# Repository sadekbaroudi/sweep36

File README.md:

# Name

sweep36

A 36 key version of the sweep, maintaining the original diodeless pcb.

# Variations

## sweeeeep

why the name sweeeeep? because an elite-c is required to support the extra features, and an elite-c has 5 additional pins... so 5 Es for the 5 extra pins. Yes, it's dumb, I know.

### Descripiton

This is a reversible pcb that is wired only, has per key leds (only on one of the two variations), oled, and choc spacing. In order to continue to support a no diode setup, I added support for the elite-c, and this is now required for the build. You can use alternative elite-c compatible controllers.

### Versions and features

There are 6 versions of this pcb, as found in the pcb/wired-rgb directory:
* choc: No hotswap, 36 keys
* choc-rotated-inner-thumb: No hotswap, 36 keys, rotated inner thumb similar to the corne
* choc-hotswap: Hotswap only, 36 keys
* ks27-choc: Support for both choc and gateron ks-27 switches, no hotswap. Note that ks-27 switches use MX keycaps on a low profile switch. Given it's choc spacing, you will likely need to use custom smaller MX keycaps if using these switches
* choc-evq-inside: No hotswap, 34 key, with an evqwgd001 roller encoder on the inside thumb key
* choc-evq-outside: No hotswap, 34 key, with an evqwgd001 roller encoder on the outside thumb key

## swweeep

So, to keep the silliness going, this is has an extra W for the wireless only, and 3 Es for the 3 extra required pins on the nice!nano.

### Description (and story)

This was created after the sweeeeep as a wireless alternative. Given the nice!nano has two less gpio than the elite-c, had to remove the data pin (and therefore TRRS). So, this is wireless only!

Given it's a wireless only build, it made sense to add nice!view support, given it consumes 1000x less power than the typical OLED. That meant that it would consume one too many gpio. In the spirit of low power consumption, removing per key rgb was a natural decision, leaving it with just enough gpio for this board.

So, backstory aside, the net of it is:
* nice!nano required
* nice!view support
* wireless only (no TRRS)
* JST spaced battery through holes
* on/off switch
* both kailh hotswap and mill max compatible through hole

Special thanks to @jasonhazel for kickstarting the initiative!

### Notes

Regarding the JST footprint, you can solder directly or use jst. If soldering, connect power to the middle hole (with the +) and GND to the -. If using JST, be sure to look at your battery wiring and connect the JST connector such that the power lines up with the middle pin (again, with thhe + on the silkscreen)

It is possible to also produce a PCB baseplate board for the swweeep with a nice silkscreen, the kicad files are [here](https://github.com/sadekbaroudi/sweep36/tree/master/sweeeeep), or if you think the [Great Wave Off Kanagawa](https://en.wikipedia.org/wiki/The_Great_Wave_off_Kanagawa) would make a good silkscreen, the gerbers for that are [here](https://github.com/sadekbaroudi/sweep36/blob/master/swweeep/swweeep-base/gerber/v1.0-kanagawa-gerbers.zip)

## dweeeeep

### Description

This was created after both of the other variations. It was created as an alternative to the sweeeeep. It's a sweeeeep with diodes. I know the principle of the original sweep was to have no diodes. I apologize, this was a special request to allow people to use a pro micro compatible controller, as they're much cheaper.

# Support me!

I have spent a lot of time and money designing prototypes, testing, developing, etc. Any contributions would be greatly appreciated!

If you don't want to, or can't afford to support me, please send me a message to let me know you've built one, along with pictures. Also, feel free to submit a pull request with pictures into this repository. I'd be happy to showcase your build.

Reddit: /u/sadekbaroudi
Discord: sadekbaroudi#1258

# Firmware

## Vial (wired version only)

Special thanks to [Jason Hazel](https://github.com/jasonhazel) for adding vial support. Note that given vial with split code takes up most of the space, there is no support for the OLED or per key RGB. If you want those features, please use QMK below.

https://github.com/sadekbaroudi/vial-qmk/tree/vial/keyboards/fingerpunch/sweeeeep

## QMK (wired version only)

https://github.com/sadekbaroudi/qmk_firmware/tree/master/keyboards/fingerpunch/sweeeeep

## ZMK (wireless version only)

https://github.com/sadekbaroudi/zmk-swweeep

# swweeep v1.3 fix

If you built a swweeep v1.3 or earlier, you will need to connect the battery ground pin to the controller gnd pin, as shown below:

# Pictures

## swweeep with nice!view

## swweeep with the base plate

## sweeeeep choc

## sweeeeep evq inside

### sweeeeep (choc)
| Front | Back |
| :---: | :---: |
|  |  |

### sweeeeep (choc-evq-inside)
| Front | Back |
| :---: | :---: |
|  |  |

### sweeeeep (choc-evq-outside)
| Front | Back |
| :---: | :---: |
|  |  |

### sweeeeep (choc-hotswap)
| Front | Back |
| :---: | :---: |
|  |  |

### sweeeeep (choc-rotated-inner-thumb)
| Front | Back |
| :---: | :---: |
|  |  |

### sweeeeep (ks27-choc)
| Front | Back |
| :---: | :---: |
|  |  |

### swweeep (choc-hotswap-optional)
| Front | Back |
| :---: | :---: |
|  |  |

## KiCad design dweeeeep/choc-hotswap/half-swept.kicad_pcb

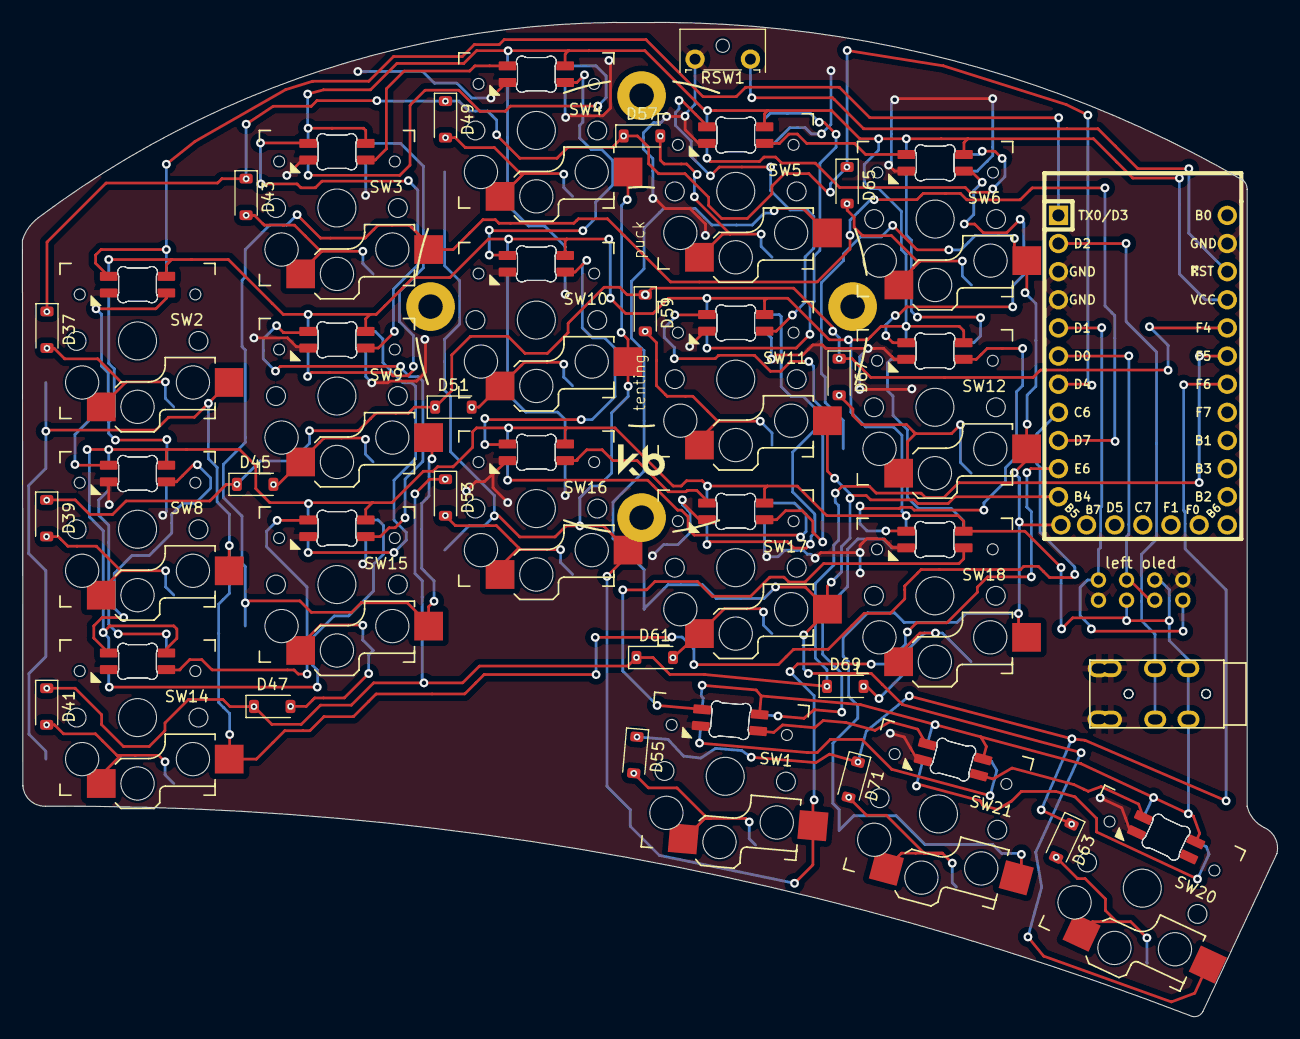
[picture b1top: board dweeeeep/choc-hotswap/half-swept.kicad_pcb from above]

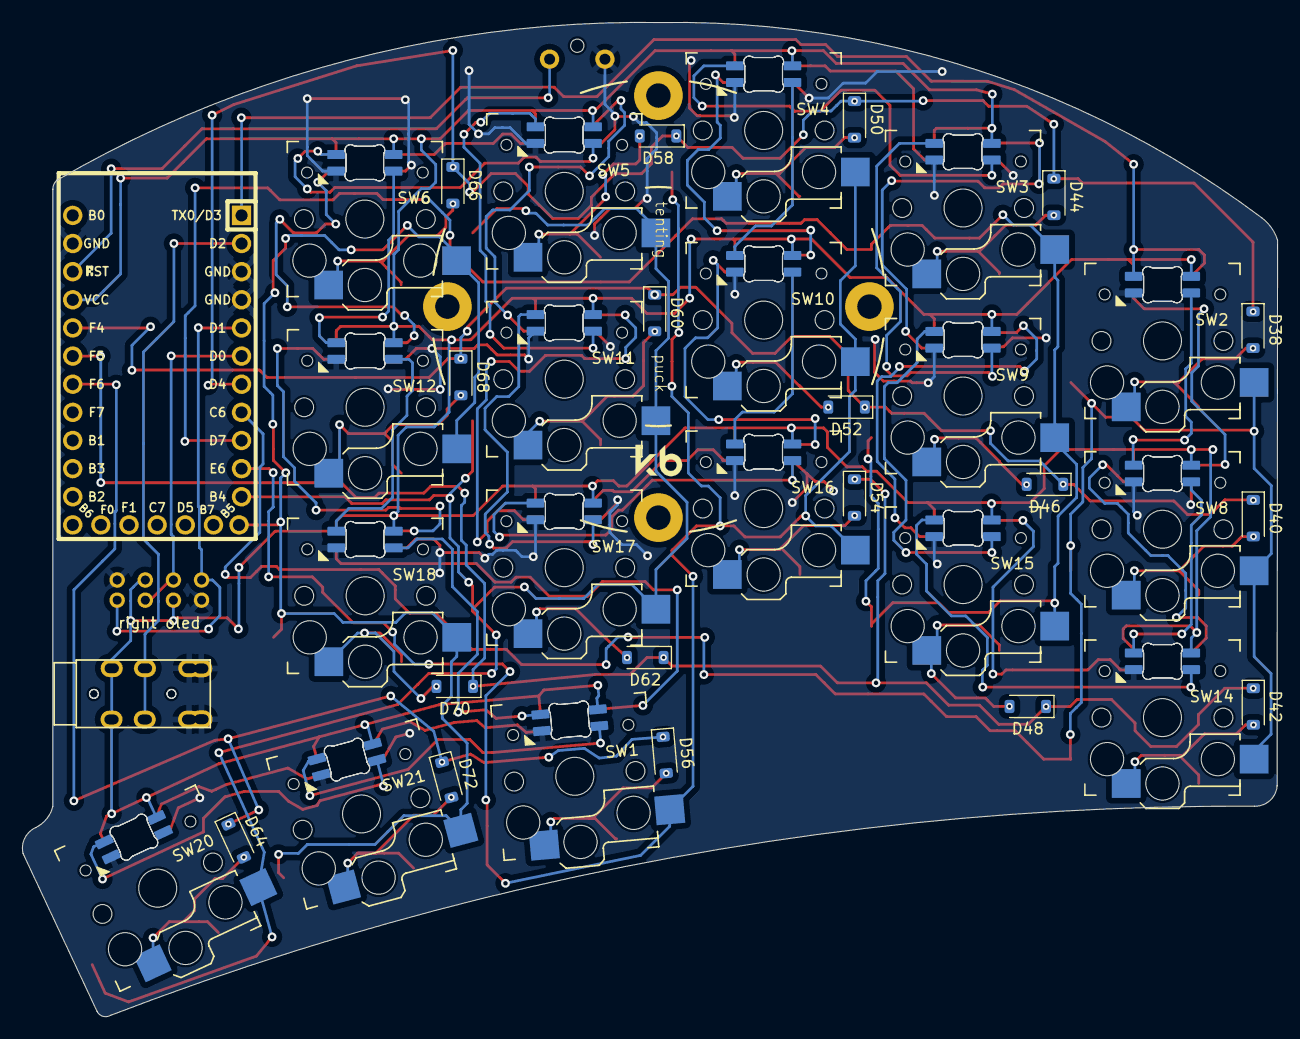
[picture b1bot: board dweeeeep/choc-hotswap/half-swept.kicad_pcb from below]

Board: 2 copper layers, 113.3 x 89.7 mm, 96 parts (38 on the bottom side), 68 nets.

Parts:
D1, D2, D3, D4, D5, D6, D7, D8, D9, D10, D11, D12, D13, D14, D15, D16, D17, D18, D19, D20, D21, D22, D23, D24, D25, D26, D27, D28, D29, D30, D31, D32, D33, D34, D35, D36: SK6812MINI-E; MX_SK6812MINI-E_REV
D37, D38, D39, D40, D41, D42, D43, D44, D45, D46, D47, D48, D49, D50, D51, D52, D53, D54, D55, D56, D57, D58, D59, D60, D61, D62, D63, D64, D65, D66, D67, D68, D69, D70, D71, D72: 1N4148W; D_SOD-123
J1, J2: AudioJack4dpb; TRRS-PJ-320A
OL1, OL2: OLED; OLED_v2
RSW1: SW_Push; SW_Tactile_SPST_Angled_MJTP1117-no-mount
SW1, SW2, SW3, SW4, SW5, SW6, SW8, SW9, SW10, SW11, SW12, SW14, SW15, SW16, SW17, SW18, SW20, SW21: SW_Push; Kailh_socket_PG1350_reversible
U2: Elite-C

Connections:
unnamed: D1.2 (DOUT), D4.4 (DIN)
unnamed: D2.2 (DOUT), D5.4 (DIN)
unnamed: D3.2 (DOUT), D6.4 (DIN)
unnamed: D4.2 (DOUT), D7.4 (DIN)
unnamed: D5.2 (DOUT), D8.4 (DIN)
unnamed: D6.2 (DOUT), D9.4 (DIN)
unnamed: D7.2 (DOUT), D10.4 (DIN)
unnamed: D10.2 (DOUT), D13.4 (DIN)
unnamed: D8.2 (DOUT), D11.4 (DIN)
unnamed: D11.2 (DOUT), D14.4 (DIN)
unnamed: D9.2 (DOUT), D12.4 (DIN)
unnamed: D12.2 (DOUT), D15.4 (DIN)
unnamed: D13.2 (DOUT), D16.4 (DIN)
unnamed: D14.2 (DOUT), D17.4 (DIN)
unnamed: D15.2 (DOUT), D18.4 (DIN)
unnamed: D2.4 (DIN), D16.2 (DOUT)
unnamed: D3.4 (DIN), D17.2 (DOUT)
unnamed: D19.2 (DOUT), D22.4 (DIN)
unnamed: D20.4 (DIN), D34.2 (DOUT)
unnamed: D20.2 (DOUT), D23.4 (DIN)
unnamed: D21.4 (DIN), D35.2 (DOUT)
unnamed: D21.2 (DOUT), D24.4 (DIN)
unnamed: D22.2 (DOUT), D25.4 (DIN)
unnamed: D23.2 (DOUT), D26.4 (DIN)
unnamed: D24.2 (DOUT), D27.4 (DIN)
unnamed: D25.2 (DOUT), D28.4 (DIN)
unnamed: D26.2 (DOUT), D29.4 (DIN)
unnamed: D27.2 (DOUT), D30.4 (DIN)
unnamed: D28.2 (DOUT), D31.4 (DIN)
unnamed: D29.2 (DOUT), D32.4 (DIN)
unnamed: D30.2 (DOUT), D33.4 (DIN)
unnamed: D31.2 (DOUT), D34.4 (DIN)
unnamed: D32.2 (DOUT), D35.4 (DIN)
unnamed: D33.2 (DOUT), D36.4 (DIN)
unnamed: D37.2 (A), D38.2 (A), SW2.1
unnamed: D39.2 (A), D40.2 (A), SW8.1
unnamed: D41.2 (A), D42.2 (A), SW14.1
unnamed: D43.2 (A), D44.2 (A), SW3.1
unnamed: D45.2 (A), D46.2 (A), SW9.1
unnamed: D47.2 (A), D48.2 (A), SW15.1
unnamed: D49.2 (A), D50.2 (A), SW4.1
unnamed: D51.2 (A), D52.2 (A), SW10.1
unnamed: D53.2 (A), D54.2 (A), SW16.1
unnamed: D55.2 (A), D56.2 (A), SW1.1
unnamed: D57.2 (A), D58.2 (A), SW5.1
unnamed: D59.2 (A), D60.2 (A), SW11.1
unnamed: D61.2 (A), D62.2 (A), SW17.1
unnamed: D63.2 (A), D64.2 (A), SW20.1
unnamed: D65.2 (A), D66.2 (A), SW6.1
unnamed: D67.2 (A), D68.2 (A), SW12.1
unnamed: D69.2 (A), D70.2 (A), SW18.1
unnamed: D71.2 (A), D72.2 (A), SW21.1
col0: SW2.2, SW8.2, SW14.2, U2.8 (5/PC6)
col1: SW3.2, SW9.2, SW15.2, U2.9 (6/PD7)
col2: SW1.2, SW4.2, SW10.2, SW16.2, U2.10 (7/PE6)
col3: SW5.2, SW11.2, SW17.2, SW20.2, U2.11 (8/PB4)
col4: SW6.2, SW12.2, SW18.2, SW21.2, U2.12 (9/PB5)
data: J1.3 (RING1), J2.3 (RING1), U2.2 (RX1/PD2)
gnd: D1.3 (VSS), D2.3 (VSS), D3.3 (VSS), D4.3 (VSS), D5.3 (VSS), D6.3 (VSS), D7.3 (VSS), D8.3 (VSS), D9.3 (VSS), D10.3 (VSS), D11.3 (VSS), D12.3 (VSS), D13.3 (VSS), D14.3 (VSS), D15.3 (VSS), D16.3 (VSS), D17.3 (VSS), D18.3 (VSS), D19.3 (VSS), D20.3 (VSS), D21.3 (VSS), D22.3 (VSS), D23.3 (VSS), D24.3 (VSS), D25.3 (VSS), D26.3 (VSS), D27.3 (VSS), D28.3 (VSS), D29.3 (VSS), D30.3 (VSS), D31.3 (VSS), D32.3 (VSS), D33.3 (VSS), D34.3 (VSS), D35.3 (VSS), D36.3 (VSS), J1.1 (SLEEVE), J1.2 (TIP), J2.1 (SLEEVE), J2.2 (TIP), OL1.4 (GND), OL2.4 (GND), RSW1.1, U2.3 (GND), U2.4 (GND), U2.23 (GND)
led: D1.4 (DIN), D19.4 (DIN), U2.1 (TX0/PD3)
reset: RSW1.2, U2.22 (RST)
row0: D37.1 (K), D38.1 (K), D43.1 (K), D44.1 (K), D49.1 (K), D50.1 (K), D57.1 (K), D58.1 (K), D65.1 (K), D66.1 (K), U2.7 (4/PD4)
row1: D39.1 (K), D40.1 (K), D45.1 (K), D46.1 (K), D51.1 (K), D52.1 (K), D59.1 (K), D60.1 (K), D67.1 (K), D68.1 (K), U2.20 (A3/PF4)
row2: D41.1 (K), D42.1 (K), D47.1 (K), D48.1 (K), D53.1 (K), D54.1 (K), D61.1 (K), D62.1 (K), D69.1 (K), D70.1 (K), U2.19 (A2/PF5)
row3: D55.1 (K), D56.1 (K), D63.1 (K), D64.1 (K), D71.1 (K), D72.1 (K), U2.18 (A1/PF6)
scl: OL1.2 (SCL), OL2.2 (SCL), U2.6 (3/PD0)
sda: OL1.1 (SDA), OL2.1 (SDA), U2.5 (2/PD1)
vcc: D1.1 (VDD), D2.1 (VDD), D3.1 (VDD), D4.1 (VDD), D5.1 (VDD), D6.1 (VDD), D7.1 (VDD), D8.1 (VDD), D9.1 (VDD), D10.1 (VDD), D11.1 (VDD), D12.1 (VDD), D13.1 (VDD), D14.1 (VDD), D15.1 (VDD), D16.1 (VDD), D17.1 (VDD), D18.1 (VDD), D19.1 (VDD), D20.1 (VDD), D21.1 (VDD), D22.1 (VDD), D23.1 (VDD), D24.1 (VDD), D25.1 (VDD), D26.1 (VDD), D27.1 (VDD), D28.1 (VDD), D29.1 (VDD), D30.1 (VDD), D31.1 (VDD), D32.1 (VDD), D33.1 (VDD), D34.1 (VDD), D35.1 (VDD), D36.1 (VDD), J1.4 (RING2), J2.4 (RING2), OL1.3 (VCC), OL2.3 (VCC), U2.21 (VCC)

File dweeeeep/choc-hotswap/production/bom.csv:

Designator,Footprint,Quantity,Value,LCSC Part #
"D1, D10, D11, D12, D13, D14, D15, D16, D17, D18, D19, D2, D20, D21, D22, D23, D24, D25, D26, D27, D28, D29, D3, D30, D31, D32, D33, D34, D35, D36, D4, D5, D6, D7, D8, D9",MX_SK6812MINI-E_REV,36,SK6812MINI-E,
"D37, D38, D39, D40, D41, D42, D43, D44, D45, D46, D47, D48, D49, D50, D51, D52, D53, D54, D55, D56, D57, D58, D59, D60, D61, D62, D63, D64, D65, D66, D67, D68, D69, D70, D71, D72",D_SOD-123,36,1N4148W,C727110
"J1, J2",TRRS-PJ-320A,2,AudioJack4dpb,
"OL1, OL2",OLED_v2,2,OLED,
RSW1,SW_Tactile_SPST_Angled_MJTP1117-no-mount,1,SW_Push,
"SW1, SW10, SW11, SW12, SW14, SW15, SW16, SW17, SW18, SW2, SW20, SW21, SW3, SW4, SW5, SW6, SW8, SW9",Kailh_socket_PG1350_reversible,18,SW_Push,
U2,Elite-C,1,Elite-C,

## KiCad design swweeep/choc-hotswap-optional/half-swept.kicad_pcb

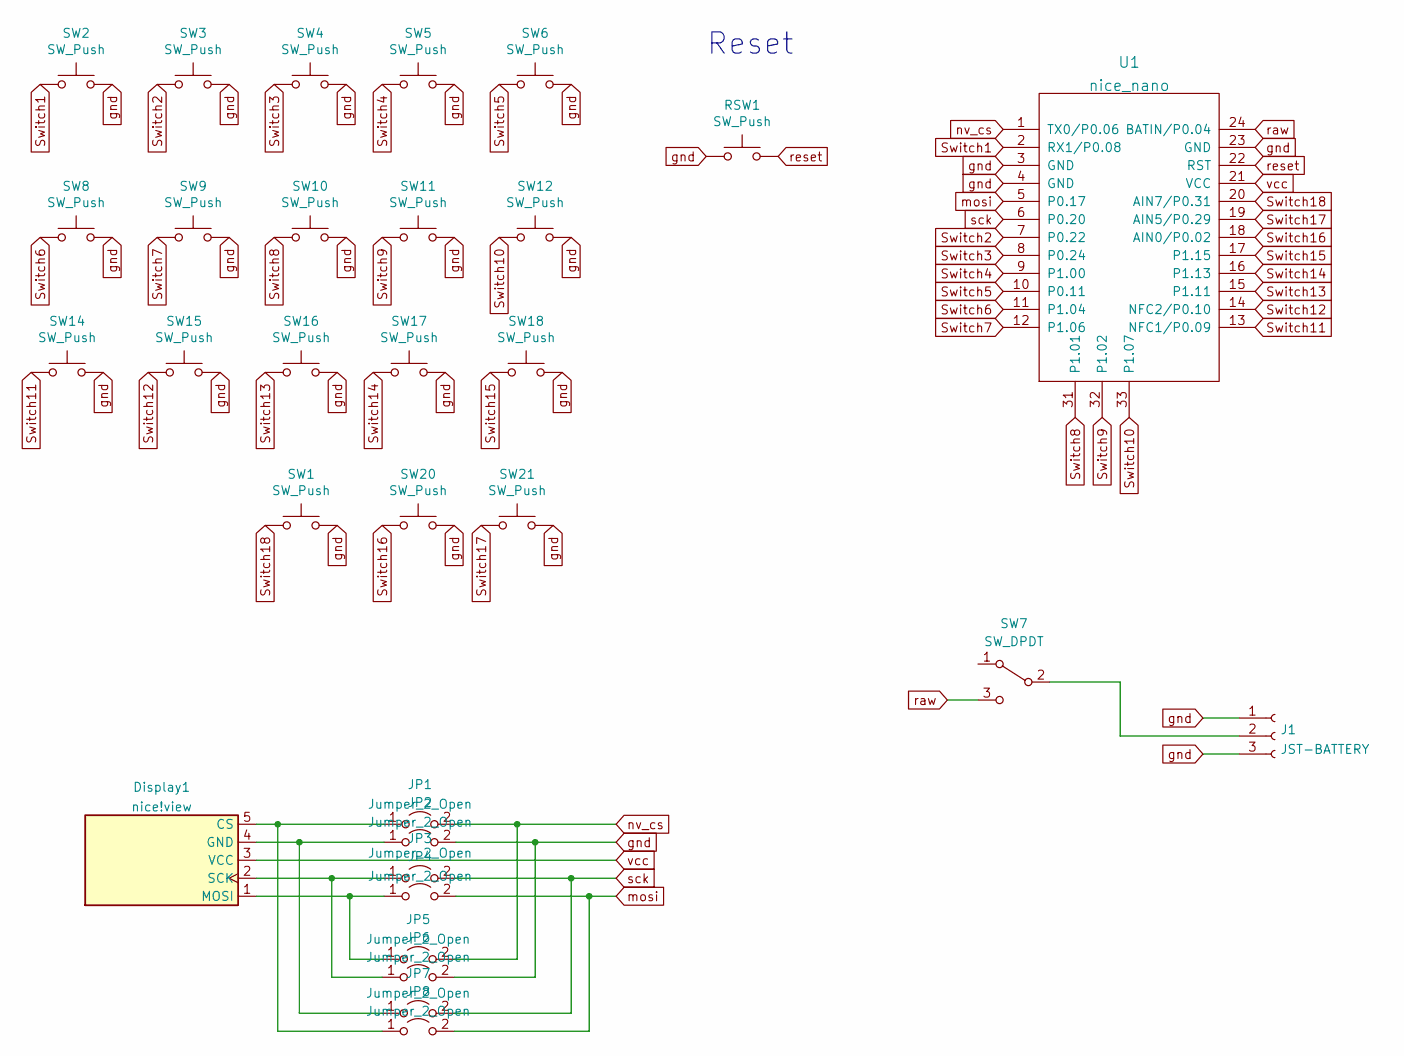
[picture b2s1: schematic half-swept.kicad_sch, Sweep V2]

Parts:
Display1: nice!view; nice_view
J1: JST-BATTERY; JST_PH_S3B-PH-K-keyboard; LCSC C157929
JP1, JP2, JP3, JP4, JP5, JP6, JP7, JP8: Jumper_2_Open; SolderJumper-2_P1.3mm_Open_TrianglePad1.0x1.5mm
RSW1: SW_Push; SW_Tactile_SPST_Angled_MJTP1117-no-mount
SW1, SW2, SW3, SW4, SW5, SW6, SW8, SW9, SW10, SW11, SW12, SW14, SW15, SW16, SW17, SW18, SW20, SW21: SW_Push; Kailh_socket_PG1350_optional_reversible_millmax
SW7: SW_DPDT; SW_CuK_OS102011MA1QN1_SPDT_Angled; LCSC C431540
U1: nice_nano

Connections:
unnamed: Display1.1 (MOSI), JP4.1 (A), JP5.1 (A)
unnamed: Display1.2 (SCK), JP3.1 (A), JP6.1 (A)
unnamed: Display1.4 (GND), JP2.1 (A), JP7.1 (A)
unnamed: Display1.5 (CS), JP1.1 (A), JP8.1 (A)
unnamed: J1.2, SW7.2 (B)
Switch1: SW2.1, U1.2 (RX1/P0.08)
Switch2: SW3.1, U1.7 (P0.22)
Switch3: SW4.1, U1.8 (P0.24)
Switch4: SW5.1, U1.9 (P1.00)
Switch5: SW6.1, U1.10 (P0.11)
Switch6: SW8.1, U1.11 (P1.04)
Switch7: SW9.1, U1.12 (P1.06)
Switch8: SW10.1, U1.31 (P1.01)
Switch9: SW11.1, U1.32 (P1.02)
Switch10: SW12.1, U1.33 (P1.07)
Switch11: SW14.1, U1.13 (NFC1/P0.09)
Switch12: SW15.1, U1.14 (NFC2/P0.10)
Switch13: SW16.1, U1.15 (P1.11)
Switch14: SW17.1, U1.16 (P1.13)
Switch15: SW18.1, U1.17 (P1.15)
Switch16: SW20.1, U1.18 (AIN0/P0.02)
Switch17: SW21.1, U1.19 (AIN5/P0.29)
Switch18: SW1.1, U1.20 (AIN7/P0.31)
gnd: J1.1, J1.3, JP2.2 (B), JP6.2 (B), RSW1.1, SW1.2, SW2.2, SW3.2, SW4.2, SW5.2, SW6.2, SW8.2, SW9.2, SW10.2, SW11.2, SW12.2, SW14.2, SW15.2, SW16.2, SW17.2, SW18.2, SW20.2, SW21.2, U1.3 (GND), U1.4 (GND), U1.23 (GND)
mosi: JP4.2 (B), JP8.2 (B), U1.5 (P0.17)
nv_cs: JP1.2 (B), JP5.2 (B), U1.1 (TX0/P0.06)
raw: SW7.3 (C), U1.24 (BATIN/P0.04)
reset: RSW1.2, U1.22 (RST)
sck: JP3.2 (B), JP7.2 (B), U1.6 (P0.20)
vcc: Display1.3 (VCC), U1.21 (VCC)

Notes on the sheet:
Reset

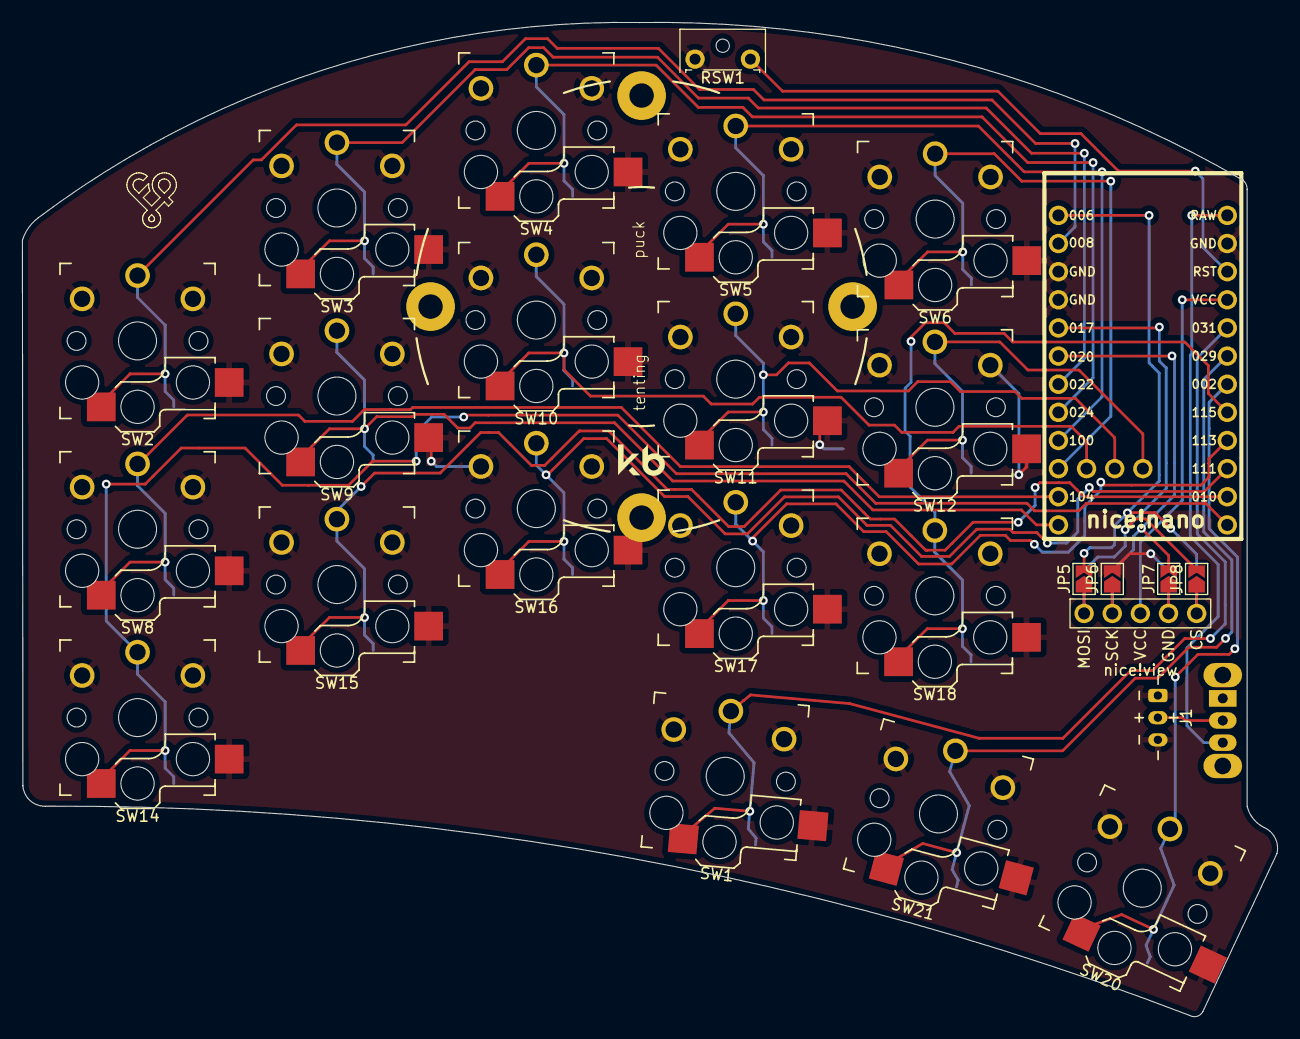
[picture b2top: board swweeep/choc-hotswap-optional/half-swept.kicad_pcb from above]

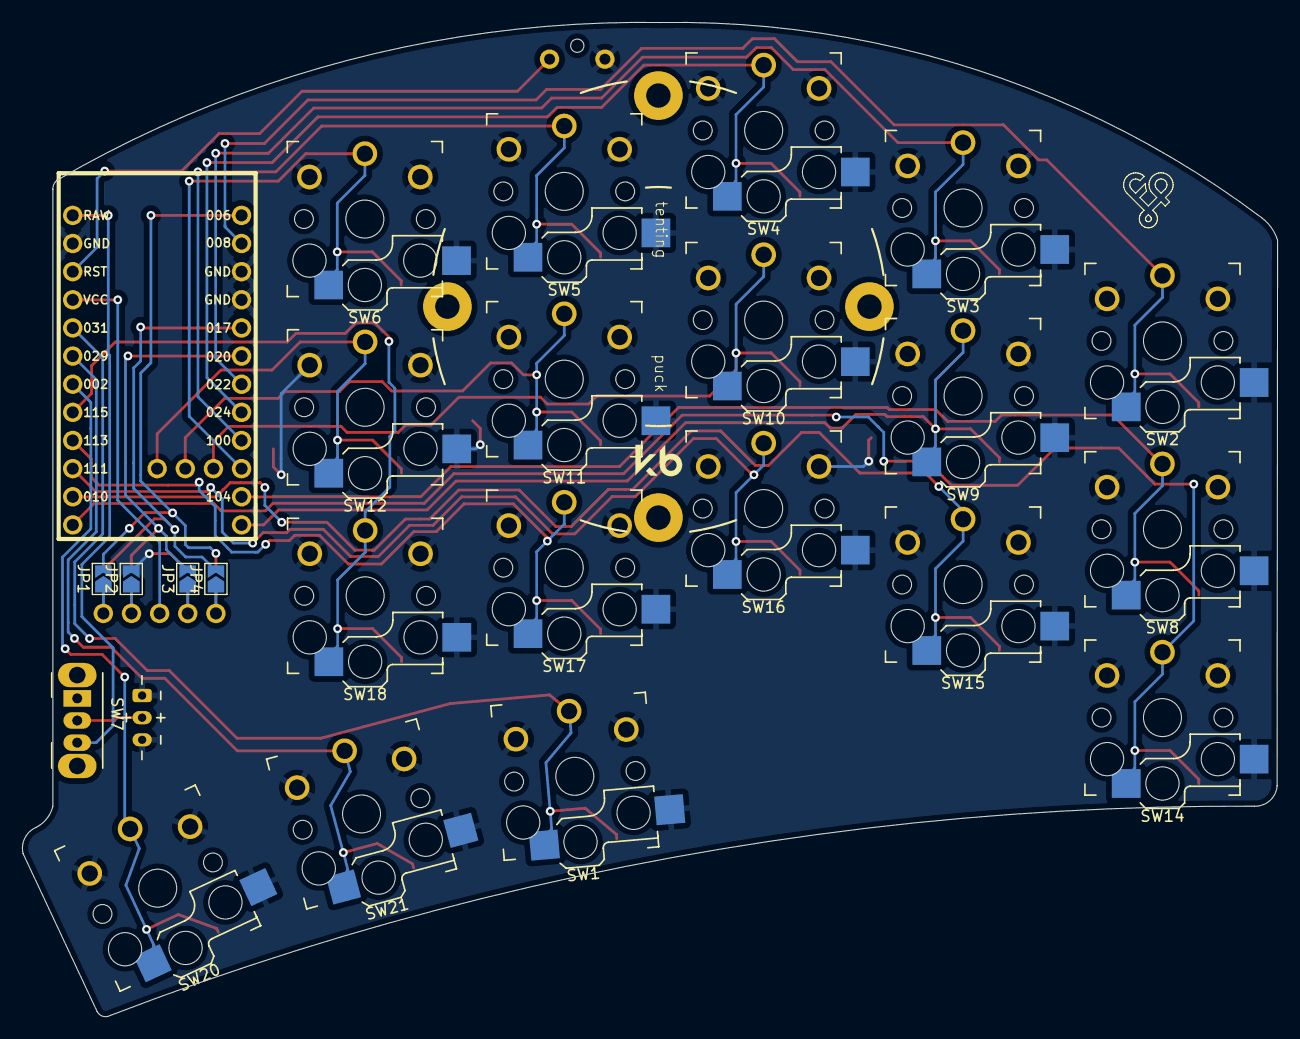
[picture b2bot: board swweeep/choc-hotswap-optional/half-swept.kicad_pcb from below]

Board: 2 copper layers, 113.3 x 89.7 mm, 31 parts (5 on the bottom side), 30 nets.

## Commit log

2022-03-12 initial commit, still needs to be tested
2022-03-13 readme commit
2022-03-13 updated to include per key led support, oled support, 36 keys, still needs routing
2022-03-14 finished routing to complete elite-c, oled, per key led, and 36 key support
2022-03-15 updated the name of the board
2022-03-18 added images
2022-04-05 added firmware link
2022-04-06 added build images
2022-04-07 added logo images
2022-04-18 added gateron ks-27 support on the same footprint, so now supports both choc v1 and ks-27
2022-04-19 converted to choc reversible hotswap
2022-04-20 made switch hole sizes a bit bigger to support mill max sockets
2022-05-06 moved pcb into subdirectory for other versions
2022-05-06 added choc hotswap version
2022-05-06 added gateron ks27 switch support, in addition to the existing choc, on the same board
2022-05-06 moved to master branch
2022-05-06 added reversible evq encoder version of the sweeeeep for lotemkw
2022-06-07 added updated readme for all the pcb versions
2022-06-16 added new slight variant with rotated inner thumb, similar to corne. allows for greater than 1U keycaps
2022-06-16 more ks-27 choc and mx footprint variations
2022-07-27 link to vial firmware
2022-10-21 added sweeeeep wireless with nice view support
2022-10-21 updated wireless sweeeeeep to support mill-max as well
2022-10-22 Change n!n pin assigmnets to match ZMK's nice_view_adapter
2022-10-22 regenerated gerbers based on gerrycave's pull request
2022-10-22 made nice view reversible with jumpers, so it's only one footprint now instead of two offset
2022-10-24 added fingerpunch logo
2022-10-24 renamed boards, updated readme, and moved directory structure to match
2022-10-24 updated zmk repo to reflect the new name
2022-10-24 Attribution to Jason Hazel for kickstarting
2022-10-25 updated footprints to have user.drawings for easier svg exports
2022-10-25 first attempt at swweeep nice view case
2022-10-25 added a filet on the nice view cover on the top left edge, per patchesweaver's request
2022-10-25 added open body version of the case
2022-10-25 added widecover version to fit battery on the side, along with step files
2022-10-26 added tenting puck support for the bottom plates
2022-10-27 added hole in bottom plate for reset switch
2022-11-05 fixed height of case and cover for battery and nice view stock header height
2022-11-05 nice view display hole was a bit too small, and on off switch hole wasn't aligned perfectly
2022-11-06 added a 3mm high bottom plate to give more space for the battery and or jst connector
2022-11-07 added step file for open body swweeep case
2022-11-10 fixed unconnected battery ground and updated readme with pics
2022-11-12 feat: adding sweep case with no nice view hole
2022-11-16 added picture, readme, and tented bottom plates for swweeep case
2022-11-16 moved the hole closer to the edge to allow space for the JST connector to go in
2022-11-22 added one more bottom plate that's 5mm thick for very large batteries
2022-11-23 first try at auto render
2022-11-23 rename workflows
2022-11-23 fix renaming artifacts
2022-11-23 Update gallery (automated)
2022-11-24 add renders to readme
2022-12-02 added 18650 holder for bottom plate
2022-12-02 replaced on off switch, from MSK12C02 to OS102011MA1QN1
2022-12-03 added on off switch extension for case
2022-12-03 thinned out the lip a bit on the large on off extension stl
2022-12-20 adding step file for on off extension
2023-01-14 Issue 6: fixed readme, was incorrect in that it said the evq variants were hotswap
2023-06-28 feat(swweeep): Add a PCB Base and project files for use as a baseplate
2023-06-28 docs(swweeep): Document additons to baseplate
2023-06-28 fix(swweeep): Resize image
2023-07-21 first iteration of dweeeeep, which is a sweeeeep with diodes
2023-09-12 docs: improve formatting
2023-10-06 added 18650 bottom plate with tenting puck holes for direct pcb mount
2023-11-11 added dweeeeep to readme
2023-11-24 added dweeeeep logo
